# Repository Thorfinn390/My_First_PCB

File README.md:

# My_First_PCB
A Mini Inverter PCB with KiCad 9.0

I learned how to design a PCB following this tutorial (https://youtu.be/d9_-lQq8ShE?si=uy9eI5YvNBUaaIL0), but it is not entirely like the tutorial.
I really liked the process, it was fun and I will definitely make more PCBs soon.

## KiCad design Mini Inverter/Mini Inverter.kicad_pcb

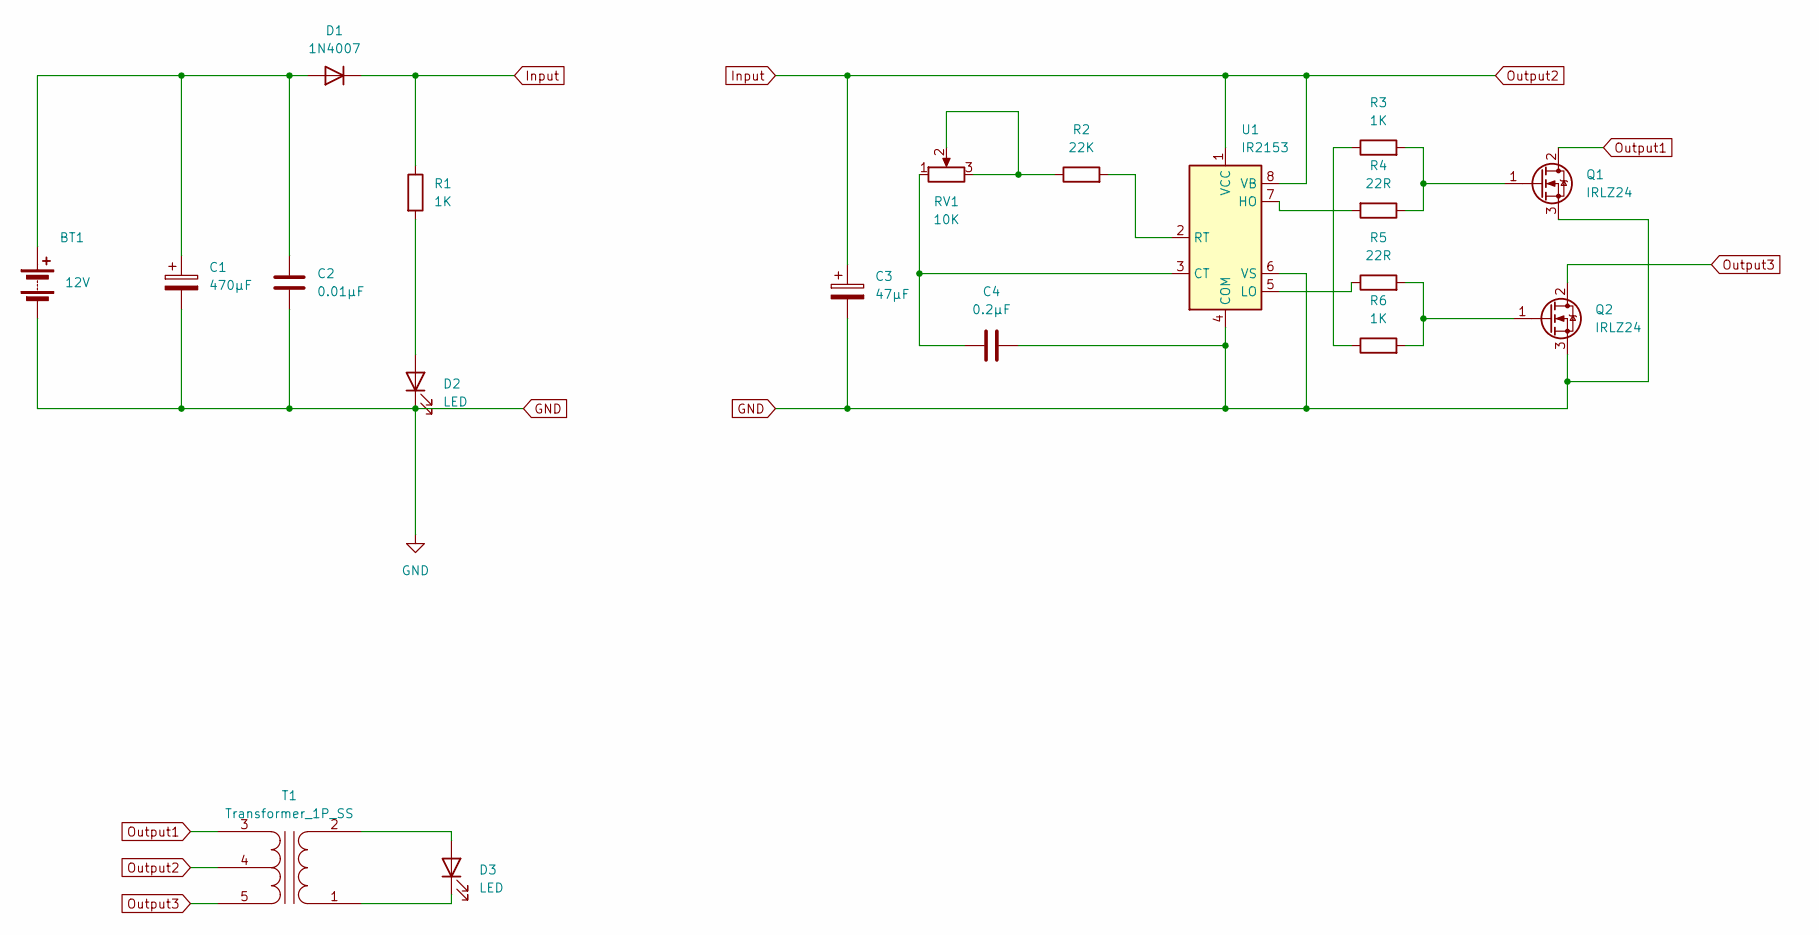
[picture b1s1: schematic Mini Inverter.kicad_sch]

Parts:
BT1: 12V; TerminalBlock_Xinya_XY308-2.54-2P_1x02_P2.54mm_Horizontal
C1: 470μF; CP_Radial_D5.0mm_P2.50mm
C2: 0.01μF; C_Disc_D3.0mm_W1.6mm_P2.50mm
C3: 47μF; CP_Radial_D5.0mm_P2.50mm
C4: 0.2μF; C_Disc_D3.0mm_W1.6mm_P2.50mm
D1: 1N4007; D_DO-41_SOD81_P10.16mm_Horizontal
D2: LED; TerminalBlock_Xinya_XY308-2.54-2P_1x02_P2.54mm_Horizontal
D3: LED; LED_D5.0mm
Q1, Q2: IRLZ24; TO-220-3_Vertical
R1, R3, R6: 1K; R_Axial_DIN0204_L3.6mm_D1.6mm_P5.08mm_Horizontal
R2: 22K; R_Axial_DIN0204_L3.6mm_D1.6mm_P5.08mm_Horizontal
R4, R5: 22R; R_Axial_DIN0204_L3.6mm_D1.6mm_P5.08mm_Horizontal
RV1: 10K; Potentiometer_ACP_CA6-H2,5_Horizontal
T1: Transformer_1P_SS; TerminalBlock_Xinya_XY308-2.54-5P_1x05_P2.54mm_Horizontal
U1: IR2153; DIP-8_W7.62mm

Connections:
GND: BT1.2 (-), C1.2, C2.2, C3.2, C4.1, D2.1 (K), Q1.3 (S), Q2.3 (S), U1.4 (COM), U1.6 (VS)
Input: C3.1, D1.1 (K), R1.1, T1.4 (SC), U1.1 (VCC), U1.8 (VB)
unnamed: BT1.1 (+), C1.1, C2.1, D1.2 (A)
unnamed: D2.2 (A), R1.2
unnamed: D3.2 (A), T1.2 (AB)
unnamed: D3.1 (K), T1.1 (AA)
unnamed: Q1.1 (G), R3.2, R4.1
unnamed: Q2.1 (G), R5.2, R6.2
unnamed: R2.1, RV1.2, RV1.3
unnamed: R3.1, R6.1
unnamed: C4.2, RV1.1, U1.3 (CT)
unnamed: R4.2, U1.7 (HO)
unnamed: R5.1, U1.5 (LO)
unnamed: R2.2, U1.2 (RT)
Output1: Q1.2 (D), T1.3 (SA)
Output3: Q2.2 (D), T1.5 (SB)

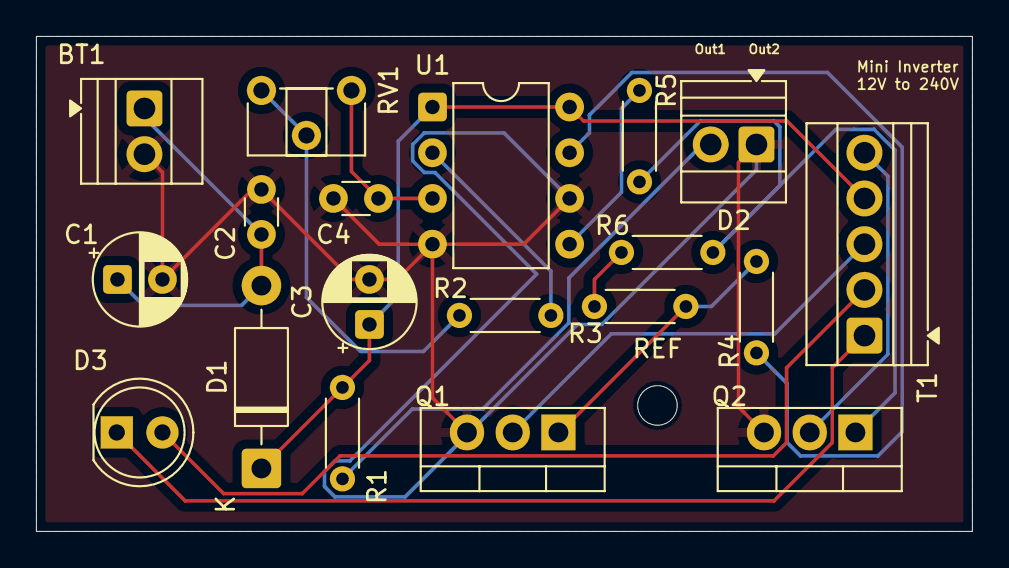
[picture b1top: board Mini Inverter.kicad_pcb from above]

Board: 2 copper layers, 52.0 x 27.5 mm, 20 parts (0 on the bottom side), 16 nets.

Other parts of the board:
REF: MountingHole_2.2mm_M2

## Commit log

2026-03-26 Enhance README with tutorial link and personal notes
    Added personal reflections and an image to the README.
2026-03-26 Add files via upload
    The step file i used.
